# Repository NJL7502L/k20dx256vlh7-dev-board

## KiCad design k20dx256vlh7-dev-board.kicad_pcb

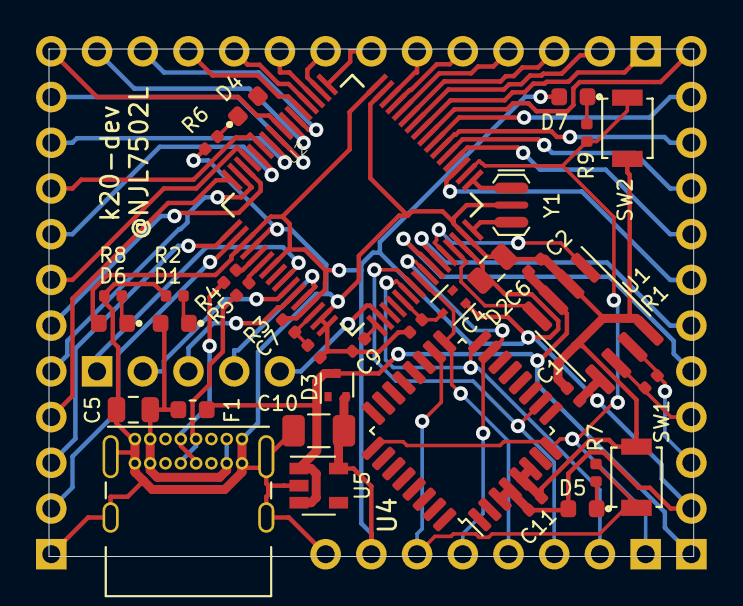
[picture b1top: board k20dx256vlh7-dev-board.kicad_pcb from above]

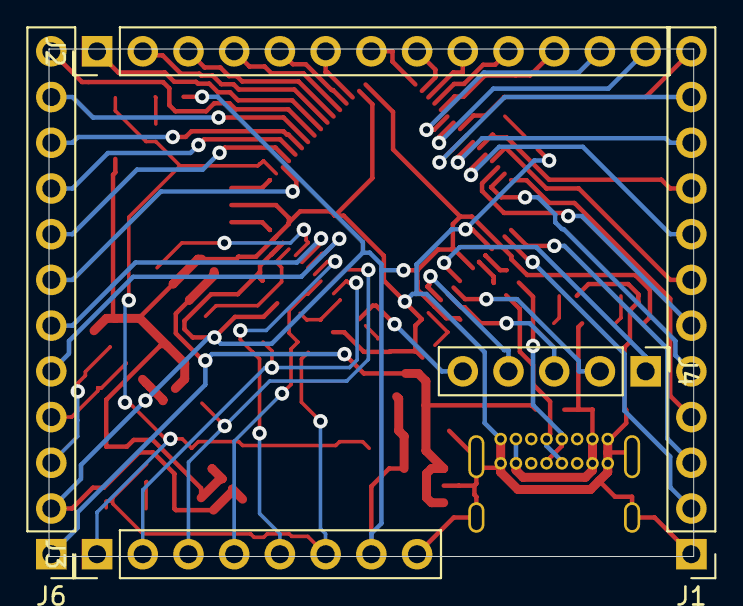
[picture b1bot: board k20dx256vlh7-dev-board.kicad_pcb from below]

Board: 2 copper layers, 35.8 x 28.2 mm, 39 parts (5 on the bottom side), 65 nets.

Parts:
C1, C2, C4, C7, C9, C11: 0.1u, 50v; C_0402_1005Metric
C5, C6: 2.2u; C_0805_2012Metric
C10: 100u,6.3v; C_1206_3216Metric
D1, D4, D5, D6, D7: LED; LED_1608_point
D2, D3: bat54c; SOT-523
F1: trip:0.75; R_0603_1608Metric
J1, J6: Conn_01x12_Male; PinHeader_1x12_P2.54mm_Vertical
J2: Conn_01x13_Male; PinHeader_1x13_P2.54mm_Vertical
J3: Conn_01x08_Male; PinHeader_1x08_P2.54mm_Vertical
J4: Conn_01x05_Male; PinHeader_1x05_P2.54mm_Vertical
J5: USB_C_Receptacle_USB2.0; USB_C_Receptacle_GCT_USB4085
R1: 120; R_0402_1005Metric
R2, R6, R7, R8, R9: R; R_0402_1005Metric
R3: 470; R_0402_1005Metric
R4, R5: 33; R_0402_1005Metric
SW1: Program; SW_SPST_B3U-1000P
SW2: Reset; SW_SPST_B3U-1000P
U1: MCP2562-E-SN; SOIC-8_3.9x4.9mm_P1.27mm
U2: MK20DX256VLH7; QFP50P1200X1200X160-64N
U4: MKL04Z32VLC4; LQFP-32_7x7mm_P0.8mm
U5: MIC5219-3.3YM5; SOT-23-5
Y1: 16MHz; CSTCE16M0V53-R0

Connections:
+3V3: C1.2, C6.1, C10.1, C11.2, D2.1, D3.2, D5.2, D6.2, D7.2, J3.7, J6.2, R3.1, U1.5, U2.3, U2.7, U2.13, U2.30, U2.48, U4.3, U4.4, U5.5
+5V: C2.2, D3.3, F1.1, J6.1, U1.3, U5.1, U5.3
/CAN+: J6.3, R1.1, U1.7
/CAN-: J6.4, R1.2, U1.6
/CAN_RX: U1.4, U2.29
/CAN_TX: U1.1, U2.28
/D0(39): J6.11, U2.39
/D1(40): J6.12, U2.40
/D2(57): J1.11, U2.57
/D5(64): J1.4, U2.64
/D6(61): J1.7, U2.61
/D7(59): J1.9, U2.59
/D8(60): J1.8, U2.60
/D9(46): J2.6, U2.46
/D10(49): J2.7, U2.49
/D11(51): J2.9, U2.51
/D12(52): J2.10, U2.52
/D13(50)_LED: J2.8, U2.50
/D14(58): J1.10, U2.58
/D15(43): J2.3, U2.43
/D16(35): J6.7, U2.35
/D17(36): J6.8, U2.36
/D18(38): J6.10, U2.38
/D19(37): J6.9, U2.37
/D20(62): J1.6, U2.62
/D21(63): J1.5, U2.63
/D22(44): J2.4, U2.44
/D23(45): J2.5, U2.45
/D24(27): J6.6, U2.27
/D25(42): J2.2, U2.42
/D26(2): J1.2, U2.2
/D27(54): J2.12, U2.54
/D28(53): J2.11, U2.53
/D29(55): J2.13, U2.55
/D30(56): J1.12, U2.56
/D31(1): J1.3, U2.1
/D32(41): J2.1, U2.41
/D33(26): J6.5, U2.26
/PTA0: J3.2, U2.22, U4.16
/PTA1: J3.3, U2.23, U4.10
/PTA2: J3.4, U2.24, U4.17
/PTA3: J3.5, U2.25, U4.15
/Program: J3.6, R7.2, SW1.1, U4.18
/RESET: J3.1, R9.2, SW2.1, U2.34, U4.8, U4.25
/USB_D+: J5.A6, J5.B6, R4.2
/USB_D-: J5.A7, J5.B7, R5.2
/USB_M: R5.1, U2.6
/USB_P: R4.1, U2.5
GND: C1.1, C2.1, C4.2, C5.2, C6.2, C7.1, C9.2, C10.2, C11.1, J1.1, J3.8, J5.A1, J5.A12, J5.B1, J5.B12, J5.S1, R2.2, R6.2, R8.2, SW1.2, SW2.2, U1.2, U1.8, U2.4, U2.15, U2.16, U2.31, U2.47, U4.5, U4.6, U5.2, Y1.2
unnamed: C4.1, D2.3, U2.21
unnamed: C5.1, D1.2, F1.2, J5.A4, J5.A9, J5.B4, J5.B9
unnamed: C7.2, R3.2, U2.14
unnamed: C9.1, U2.17
unnamed: D1.1, R2.1
unnamed: D4.1, R6.1
unnamed: D5.1, R7.1
unnamed: D6.1, R8.1
unnamed: D7.1, R9.1
unnamed: J4.1, U2.9
unnamed: J4.2, U2.10
unnamed: J4.3, U2.11
unnamed: J4.4, U2.12
unnamed: J4.5, U2.18
unnamed: U2.32, Y1.3
unnamed: U2.33, Y1.1

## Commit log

2020-09-03 zsh init: rename files
2020-09-03 zsh init: add submodule kicad
2020-09-03 zsh init: add submodule digikey
2020-09-03 回路図を記述した
2020-09-03 フットプリントの割当、アノテーション、ネットリストの生成
2020-09-03 ネットリストの読み込み
2020-09-05 回路図を更新
2020-09-06 フットプリントの変更
2020-09-12 回路図の見直し
2020-09-12 回路図に追記
2020-09-13 発注した！
2020-10-03 各種抵抗・コンデンサの値を決定
